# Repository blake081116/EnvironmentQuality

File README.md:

# EnvironmentQuality

Arduino Nano ESP32 indoor environment monitor with BME688, MAX4466, SPS30, OLED display, and a FastAPI dashboard.

## Dashboard

The dashboard lives in the `dashboard` directory and is built with FastAPI.

### Environment Setup

Option 1: use `pip`.

```bash
python -m venv .venv
source .venv/bin/activate
pip install -r dashboard/requirements.txt
```

Option 2: use `conda`.

```bash
conda env create -f environment.yml
conda activate csci561
```

### Run With Demo Data

If no device is connected, run the dashboard in demo mode:

```bash
uvicorn dashboard.app:app --reload
```

Open:

```text
http://127.0.0.1:8000
```

### Run With Device Data

#### Option 1: Wireless Mode

Use this mode when the Nano ESP32 is powered separately and is not connected to your Mac over USB.

In `main.ino/main.ino.ino`, set your Wi-Fi credentials and dashboard URL:

```cpp
const char* WIFI_SSID = "Your_WiFi_Name";
const char* WIFI_PASSWORD = "Your_WiFi_Password";
const char* API_URL = "http://YOUR_MAC_IP:8000/api/push";
```

Find your Mac Wi-Fi IP address:

```bash
ipconfig getifaddr en0
```

For example, if the command returns `192.168.1.25`, set:

```cpp
const char* API_URL = "http://192.168.1.25:8000/api/push";
```

Start the dashboard so it accepts requests from devices on the same Wi-Fi network:

```bash
uvicorn dashboard.app:app --host 0.0.0.0 --port 8000 --reload
```

Open on your Mac:

```text
http://127.0.0.1:8000
```

Or open from another device on the same network:

```text
http://YOUR_MAC_IP:8000
```

Wireless mode notes:

- The Nano ESP32 still needs power from a battery, USB power adapter, or another external source.
- The Mac and Nano ESP32 must be on the same Wi-Fi network.
- If the dashboard does not receive data, check that macOS Firewall allows Python/uvicorn to accept incoming connections.
- If your Mac IP changes, update `API_URL` and upload the firmware again.

#### Option 2: USB Serial Mode

Use this mode when the Arduino/Nano ESP32 is connected to your Mac over USB.

Automatically find the serial port:

```bash
SERIAL_PORT=auto uvicorn dashboard.app:app --reload
```

Or specify the port manually, for example on macOS:

```bash
SERIAL_PORT=/dev/cu.usbmodem206EF131BCA82 uvicorn dashboard.app:app --reload
```

The default serial baud rate is `115200`. To override it:

```bash
SERIAL_PORT=auto SERIAL_BAUD=115200 uvicorn dashboard.app:app --reload
```

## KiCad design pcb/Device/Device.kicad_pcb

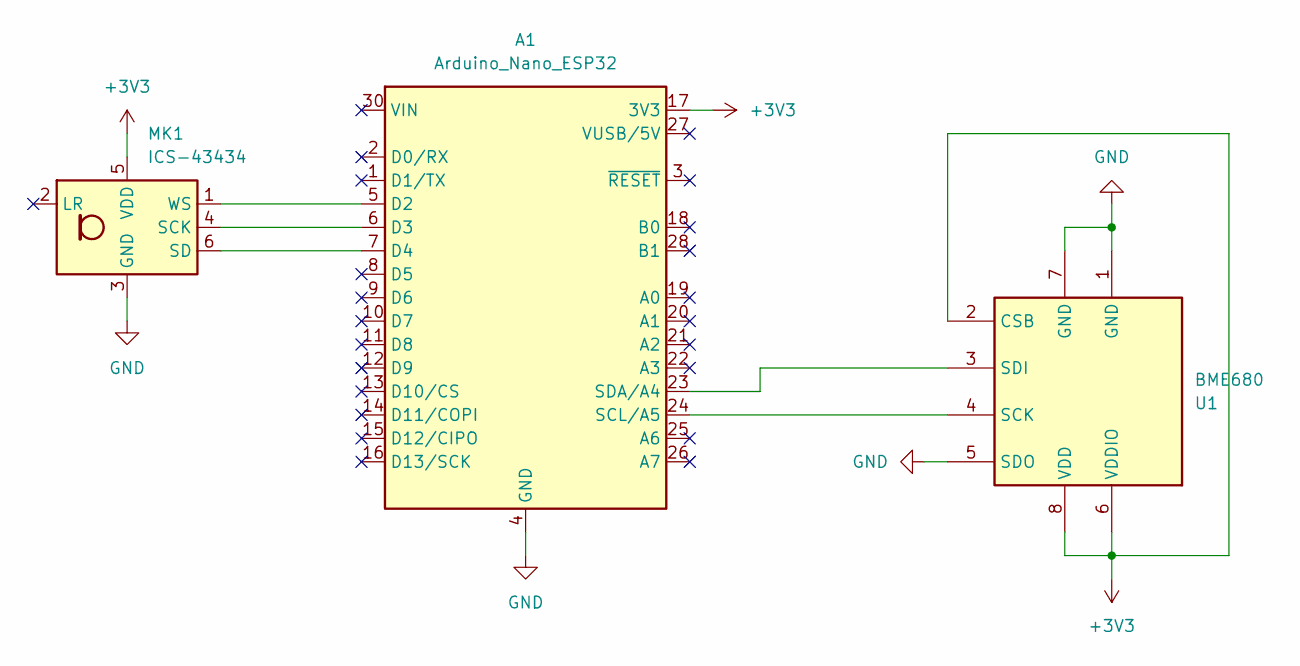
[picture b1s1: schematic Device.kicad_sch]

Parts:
A1: Arduino_Nano_ESP32; Arduino_Nano
MK1: ICS-43434; InvenSense_ICS-43434-6_3.5x2.65mm
U1: BME680; Bosch_LGA-8_3x3mm_P0.8mm_ClockwisePinNumbering

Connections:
+3V3: A1.17 (3V3), MK1.5 (VDD), U1.2 (CSB), U1.6 (VDDIO), U1.8 (VDD)
GND: A1.4 (GND), A1.29 (GND), MK1.3 (GND), U1.1 (GND), U1.5 (SDO), U1.7 (GND)
unnamed: A1.5 (D2), MK1.1 (WS)
unnamed: A1.6 (D3), MK1.4 (SCK)
unnamed: A1.7 (D4), MK1.6 (SD)
unnamed: A1.24 (SCL/A5), U1.4 (SCK)
unnamed: A1.23 (SDA/A4), U1.3 (SDI)

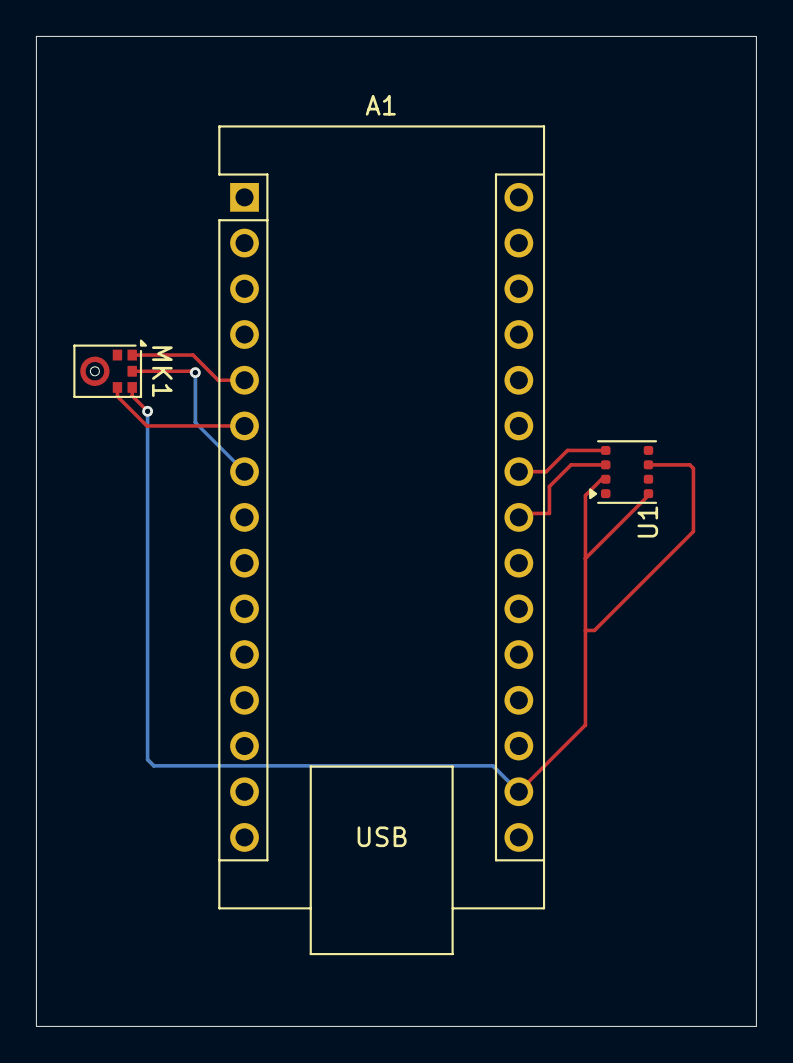
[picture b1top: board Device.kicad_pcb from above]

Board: 2 copper layers, 40.0 x 55.0 mm, 3 parts (0 on the bottom side), 7 nets.

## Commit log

2026-03-16 [UPLOAD] Upload preliminary pcb design
2026-04-17 [UPDATE] adding new sensor (mic)
2026-04-28 [UPDATE] Major update for this project
2026-04-28 [ADJUST] Minor adjustment for readme
2026-04-29 [UPDATE] update on website and main ino
